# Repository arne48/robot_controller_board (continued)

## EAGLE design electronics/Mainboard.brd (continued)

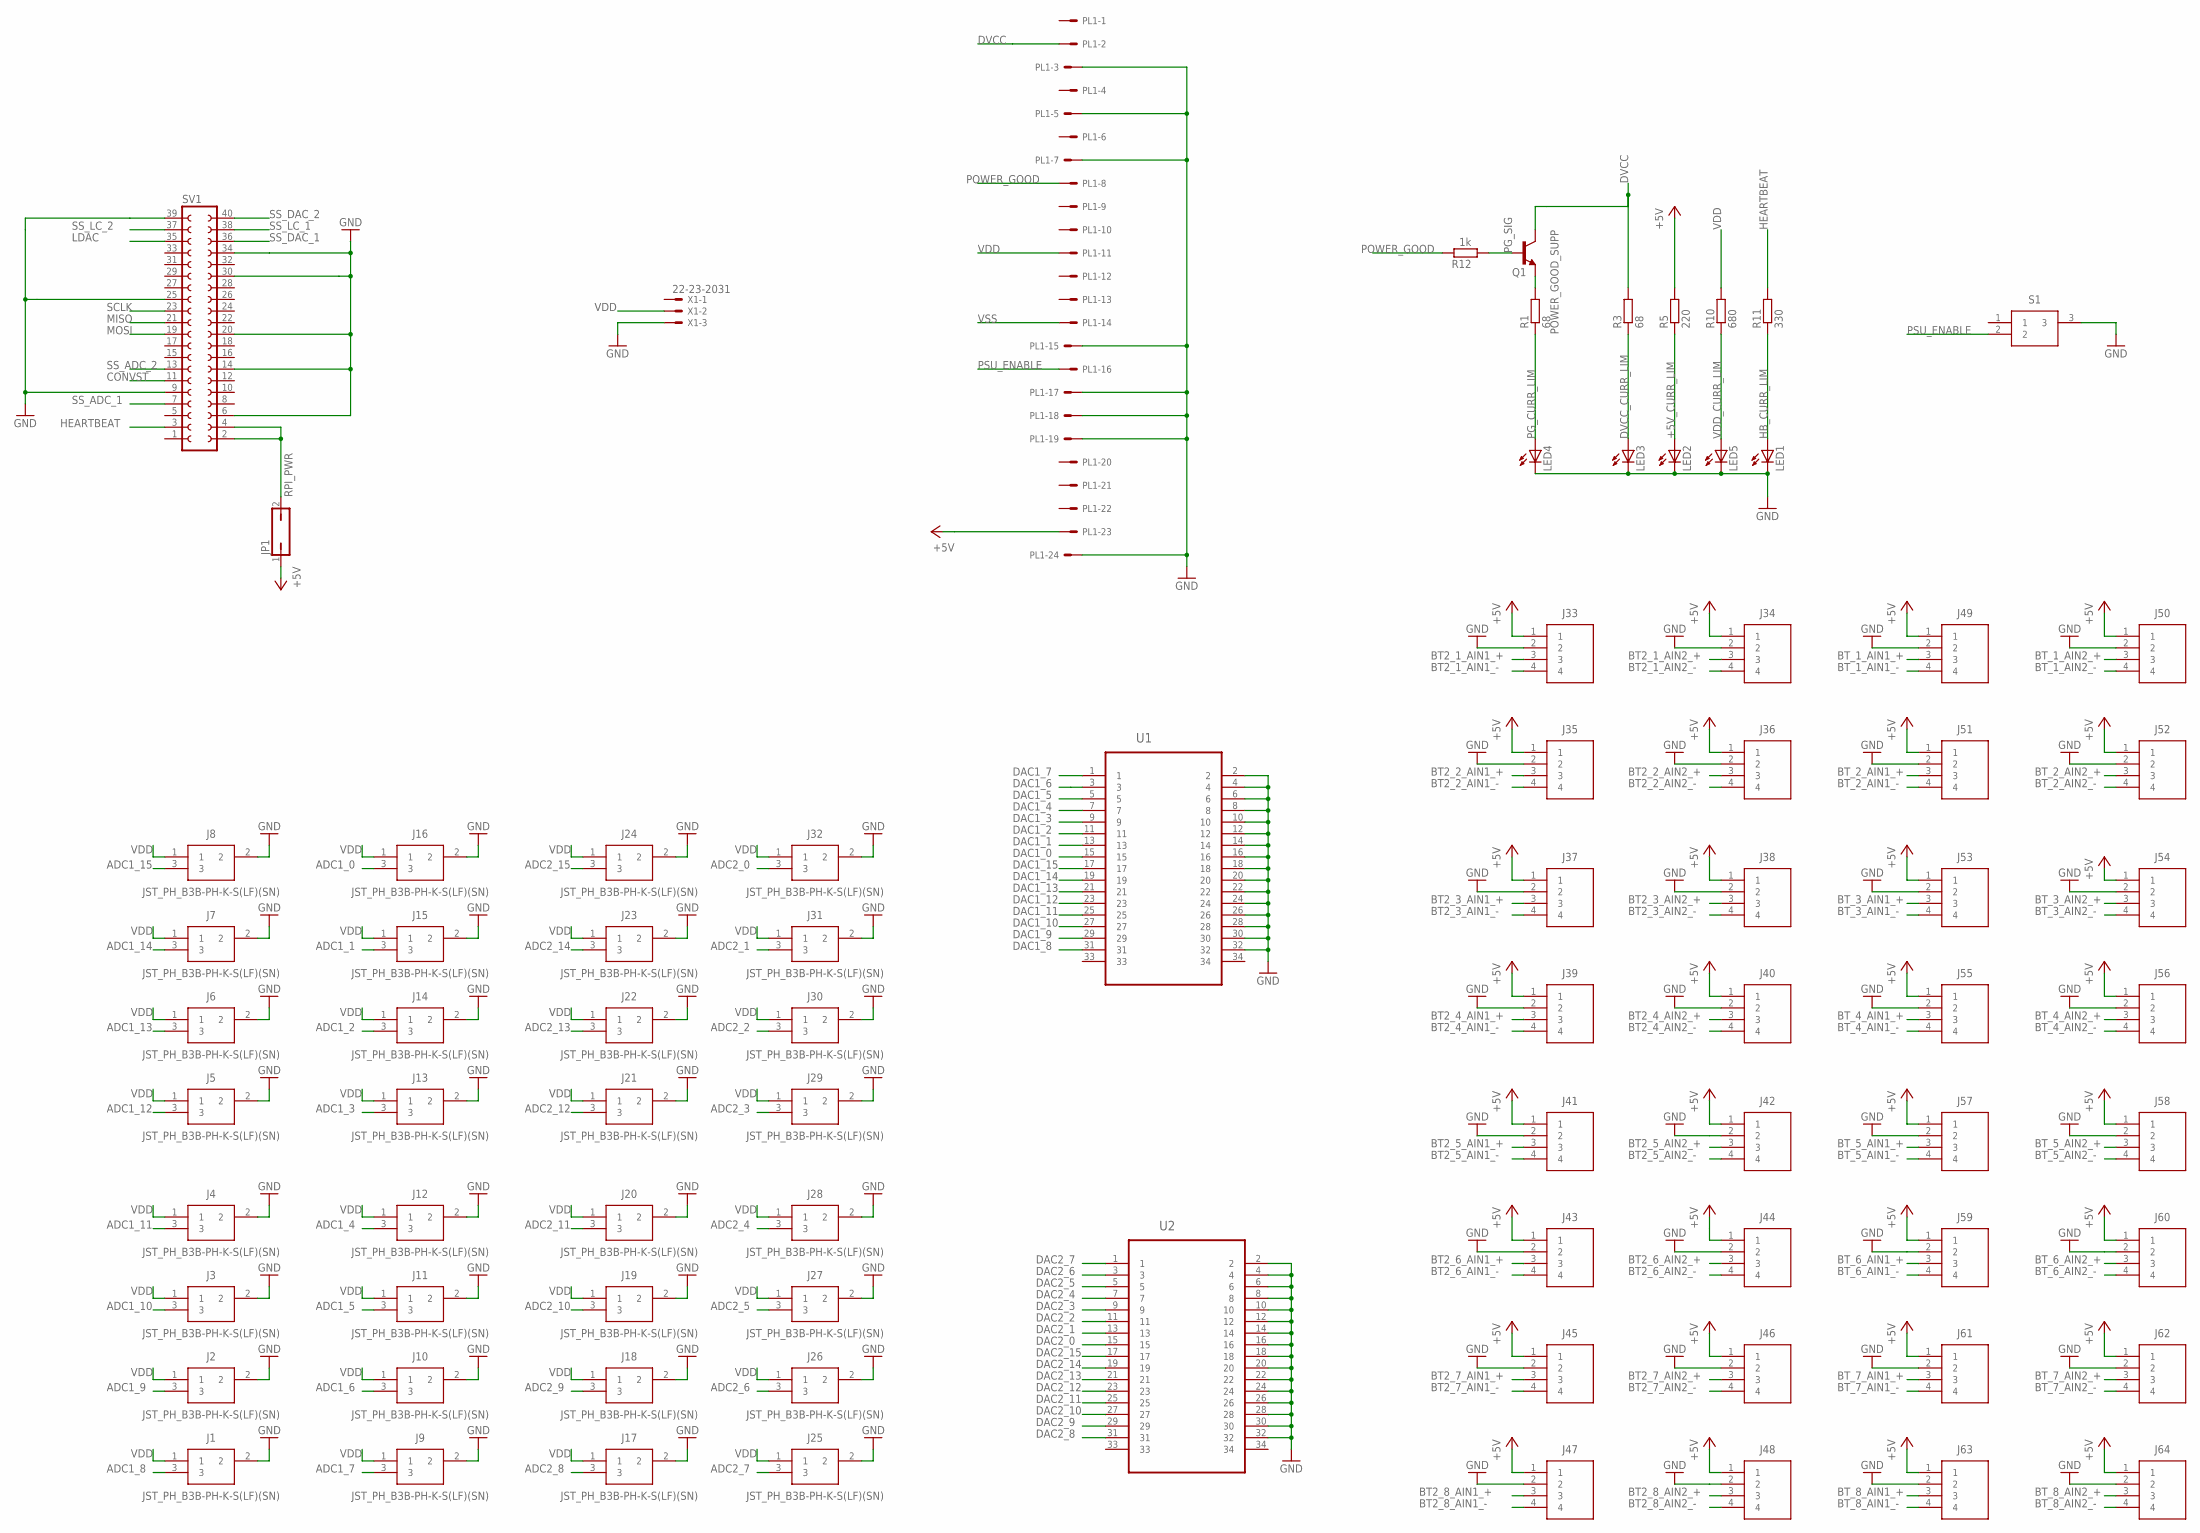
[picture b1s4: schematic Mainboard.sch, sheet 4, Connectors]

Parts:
J1, J2, J3, J4, J5, J6, J7, J8, J9, J10, J11, J12, J13, J14, J15, J16, J17, J18, J19, J20, J21, J22, J23, J24, J25, J26, J27, J28, J29, J30, J31, J32: JST_PH_B3B-PH-K-S(LF)(SN); JST_PH_SHDR3W50P0X200_1X3_790X450X600
J33, J34, J35, J36, J37, J38, J39, J40, J41, J42, J43, J44, J45, J46, J47, J48, J49, J50, J51, J52, J53, J54, J55, J56, J57, J58, J59, J60, J61, J62, J63, J64: B4B-PH-K-S(LF)(SN); SHDR4W50P0X200_1X4_990X450X600
JP1: JP1Q; JP1
LED1, LED2, LED3, LED4, LED5: LEDCHIP-LED0603; CHIP-LED0603
PL1: 555X-24V; 5566-24
Q1: BCF29SMD; SOT23-BEC
R1, R3: 68; R0805
R5: 220; R0805
R10: 680; R0805
R11: 330; R0805
R12: 1k; R0805
S1: 1MS1T1B1M2QES-5
SV1: FE20-2
U1, U2: AMP-5103309-7-34PIN_5103309-7; AMP-5103309-7-34PIN_TYCO_5103309-7
X1: 22-23-2031

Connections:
+5V: J33.1, J34.1, J35.1, J36.1, J37.1, J38.1, J39.1, J40.1, J41.1, J42.1, J43.1, J44.1, J45.1, J46.1, J47.1, J48.1, J49.1, J50.1, J51.1, J52.1, J53.1, J54.1, J55.1, J56.1, J57.1, J58.1, J59.1, J60.1, J61.1, J62.1, J63.1, J64.1, JP1.1, PL1.23, R5.2; also elsewhere on the board
+5V_CURR_LIM: LED2.A, R5.1
ADC1_0: J16.3; also elsewhere on the board
ADC1_1: J15.3; also elsewhere on the board
ADC1_2: J14.3; also elsewhere on the board
ADC1_3: J13.3; also elsewhere on the board
ADC1_4: J12.3; also elsewhere on the board
ADC1_5: J11.3; also elsewhere on the board
ADC1_6: J10.3; also elsewhere on the board
ADC1_7: J9.3; also elsewhere on the board
ADC1_8: J1.3; also elsewhere on the board
ADC1_9: J2.3; also elsewhere on the board
ADC1_10: J3.3; also elsewhere on the board
ADC1_11: J4.3; also elsewhere on the board
ADC1_12: J5.3; also elsewhere on the board
ADC1_13: J6.3; also elsewhere on the board
ADC1_14: J7.3; also elsewhere on the board
ADC1_15: J8.3; also elsewhere on the board
ADC2_0: J32.3; also elsewhere on the board
ADC2_1: J31.3; also elsewhere on the board
ADC2_2: J30.3; also elsewhere on the board
ADC2_3: J29.3; also elsewhere on the board
ADC2_4: J28.3; also elsewhere on the board
ADC2_5: J27.3; also elsewhere on the board
ADC2_6: J26.3; also elsewhere on the board
ADC2_7: J25.3; also elsewhere on the board
ADC2_8: J17.3; also elsewhere on the board
ADC2_9: J18.3; also elsewhere on the board
ADC2_10: J19.3; also elsewhere on the board
ADC2_11: J20.3; also elsewhere on the board
ADC2_12: J21.3; also elsewhere on the board
ADC2_13: J22.3; also elsewhere on the board
ADC2_14: J23.3; also elsewhere on the board
ADC2_15: J24.3; also elsewhere on the board
BT2_1_AIN1_+: J33.3; also elsewhere on the board
BT2_1_AIN1_-: J33.4; also elsewhere on the board
BT2_1_AIN2_+: J34.3; also elsewhere on the board
BT2_1_AIN2_-: J34.4; also elsewhere on the board
BT2_2_AIN1_+: J35.3; also elsewhere on the board
BT2_2_AIN1_-: J35.4; also elsewhere on the board
BT2_2_AIN2_+: J36.3; also elsewhere on the board
BT2_2_AIN2_-: J36.4; also elsewhere on the board
BT2_3_AIN1_+: J37.3; also elsewhere on the board
BT2_3_AIN1_-: J37.4; also elsewhere on the board
BT2_3_AIN2_+: J38.3; also elsewhere on the board
BT2_3_AIN2_-: J38.4; also elsewhere on the board
BT2_4_AIN1_+: J39.3; also elsewhere on the board
BT2_4_AIN1_-: J39.4; also elsewhere on the board
BT2_4_AIN2_+: J40.3; also elsewhere on the board
BT2_4_AIN2_-: J40.4; also elsewhere on the board
BT2_5_AIN1_+: J41.3; also elsewhere on the board
BT2_5_AIN1_-: J41.4; also elsewhere on the board
BT2_5_AIN2_+: J42.3; also elsewhere on the board
BT2_5_AIN2_-: J42.4; also elsewhere on the board
BT2_6_AIN1_+: J43.3; also elsewhere on the board
BT2_6_AIN1_-: J43.4; also elsewhere on the board
BT2_6_AIN2_+: J44.3; also elsewhere on the board
BT2_6_AIN2_-: J44.4; also elsewhere on the board
BT2_7_AIN1_+: J45.3; also elsewhere on the board
BT2_7_AIN1_-: J45.4; also elsewhere on the board
BT2_7_AIN2_+: J46.3; also elsewhere on the board
BT2_7_AIN2_-: J46.4; also elsewhere on the board
BT2_8_AIN1_+: J47.3; also elsewhere on the board
BT2_8_AIN1_-: J47.4; also elsewhere on the board
BT2_8_AIN2_+: J48.3; also elsewhere on the board
BT2_8_AIN2_-: J48.4; also elsewhere on the board
BT_1_AIN1_+: J49.3; also elsewhere on the board
BT_1_AIN1_-: J49.4; also elsewhere on the board
BT_1_AIN2_+: J50.3; also elsewhere on the board
BT_1_AIN2_-: J50.4; also elsewhere on the board
BT_2_AIN1_+: J51.3; also elsewhere on the board
BT_2_AIN1_-: J51.4; also elsewhere on the board
BT_2_AIN2_+: J52.3; also elsewhere on the board
BT_2_AIN2_-: J52.4; also elsewhere on the board
BT_3_AIN1_+: J53.3; also elsewhere on the board
BT_3_AIN1_-: J53.4; also elsewhere on the board
BT_3_AIN2_+: J54.3; also elsewhere on the board
BT_3_AIN2_-: J54.4; also elsewhere on the board
BT_4_AIN1_+: J55.3; also elsewhere on the board
BT_4_AIN1_-: J55.4; also elsewhere on the board
BT_4_AIN2_+: J56.3; also elsewhere on the board
BT_4_AIN2_-: J56.4; also elsewhere on the board
BT_5_AIN1_+: J57.3; also elsewhere on the board
BT_5_AIN1_-: J57.4; also elsewhere on the board
BT_5_AIN2_+: J58.3; also elsewhere on the board
BT_5_AIN2_-: J58.4; also elsewhere on the board
BT_6_AIN1_+: J59.3; also elsewhere on the board
BT_6_AIN1_-: J59.4; also elsewhere on the board
BT_6_AIN2_+: J60.3; also elsewhere on the board
BT_6_AIN2_-: J60.4; also elsewhere on the board
BT_7_AIN1_+: J61.3; also elsewhere on the board
BT_7_AIN1_-: J61.4; also elsewhere on the board
BT_7_AIN2_+: J62.3; also elsewhere on the board
BT_7_AIN2_-: J62.4; also elsewhere on the board
BT_8_AIN1_+: J63.3; also elsewhere on the board
BT_8_AIN1_-: J63.4; also elsewhere on the board
BT_8_AIN2_+: J64.3; also elsewhere on the board
BT_8_AIN2_-: J64.4; also elsewhere on the board
CONVST: SV1.11; also elsewhere on the board
DAC1_0: U1.15; also elsewhere on the board
DAC1_1: U1.13; also elsewhere on the board
DAC1_2: U1.11; also elsewhere on the board
DAC1_3: U1.9; also elsewhere on the board
DAC1_4: U1.7; also elsewhere on the board
DAC1_5: U1.5; also elsewhere on the board
DAC1_6: U1.3; also elsewhere on the board
DAC1_7: U1.1; also elsewhere on the board
DAC1_8: U1.31; also elsewhere on the board
DAC1_9: U1.29; also elsewhere on the board
DAC1_10: U1.27; also elsewhere on the board
DAC1_11: U1.25; also elsewhere on the board
DAC1_12: U1.23; also elsewhere on the board
DAC1_13: U1.21; also elsewhere on the board
DAC1_14: U1.19; also elsewhere on the board
DAC1_15: U1.17; also elsewhere on the board
DAC2_0: U2.15; also elsewhere on the board
DAC2_1: U2.13; also elsewhere on the board
DAC2_2: U2.11; also elsewhere on the board
DAC2_3: U2.9; also elsewhere on the board
DAC2_4: U2.7; also elsewhere on the board
DAC2_5: U2.5; also elsewhere on the board
DAC2_6: U2.3; also elsewhere on the board
DAC2_7: U2.1; also elsewhere on the board
DAC2_8: U2.31; also elsewhere on the board
DAC2_9: U2.29; also elsewhere on the board
DAC2_10: U2.27; also elsewhere on the board
DAC2_11: U2.25; also elsewhere on the board
DAC2_12: U2.23; also elsewhere on the board
DAC2_13: U2.21; also elsewhere on the board
DAC2_14: U2.19; also elsewhere on the board
DAC2_15: U2.17; also elsewhere on the board
DVCC: PL1.2, Q1.C, R3.2; also elsewhere on the board
DVCC_CURR_LIM: LED3.A, R3.1
GND: J1.2, J2.2, J3.2, J4.2, J5.2, J6.2, J7.2, J8.2, J9.2, J10.2, J11.2, J12.2, J13.2, J14.2, J15.2, J16.2, J17.2, J18.2, J19.2, J20.2, J21.2, J22.2, J23.2, J24.2, J25.2, J26.2, J27.2, J28.2, J29.2, J30.2, J31.2, J32.2, J33.2, J34.2, J35.2, J36.2, J37.2, J38.2, J39.2, J40.2, J41.2, J42.2, J43.2, J44.2, J45.2, J46.2, J47.2, J48.2, J49.2, J50.2, J51.2, J52.2, J53.2, J54.2, J55.2, J56.2, J57.2, J58.2, J59.2, J60.2, J61.2, J62.2, J63.2, J64.2, LED1.C, LED2.C, LED3.C, LED4.C, LED5.C, PL1.3, PL1.5, PL1.7, PL1.15, PL1.17, PL1.18, PL1.19, PL1.24, S1.3, SV1.6, SV1.9, SV1.14, SV1.20, SV1.25, SV1.30, SV1.34, SV1.39, U1.2, U1.4, U1.6, U1.8, U1.10, U1.12, U1.14, U1.16, U1.18, U1.20, U1.22, U1.24, U1.26, U1.28, U1.30, U1.32, U2.2, U2.4, U2.6, U2.8, U2.10, U2.12, U2.14, U2.16, U2.18, U2.20, U2.22, U2.24, U2.26, U2.28, U2.30, U2.32, X1.3; also elsewhere on the board
HB_CURR_LIM: LED1.A, R11.1
HEARTBEAT: R11.2, SV1.3
LDAC: SV1.35; also elsewhere on the board
MISO: SV1.21; also elsewhere on the board
MOSI: SV1.19; also elsewhere on the board
PG_CURR_LIM: LED4.A, R1.1
PG_SIG: Q1.B, R12.1
POWER_GOOD: PL1.8, R12.2
POWER_GOOD_SUPP: Q1.E, R1.2
PSU_ENABLE: PL1.16, S1.2
RPI_PWR: JP1.2, SV1.2, SV1.4
SCLK: SV1.23; also elsewhere on the board
SS_ADC_1: SV1.7; also elsewhere on the board
SS_ADC_2: SV1.13; also elsewhere on the board
SS_DAC_1: SV1.36; also elsewhere on the board
SS_DAC_2: SV1.40; also elsewhere on the board
SS_LC_1: SV1.38; also elsewhere on the board
SS_LC_2: SV1.37; also elsewhere on the board
VDD: J1.1, J2.1, J3.1, J4.1, J5.1, J6.1, J7.1, J8.1, J9.1, J10.1, J11.1, J12.1, J13.1, J14.1, J15.1, J16.1, J17.1, J18.1, J19.1, J20.1, J21.1, J22.1, J23.1, J24.1, J25.1, J26.1, J27.1, J28.1, J29.1, J30.1, J31.1, J32.1, PL1.11, R10.2, X1.2; also elsewhere on the board
VDD_CURR_LIM: LED5.A, R10.1
VSS: PL1.14; also elsewhere on the board

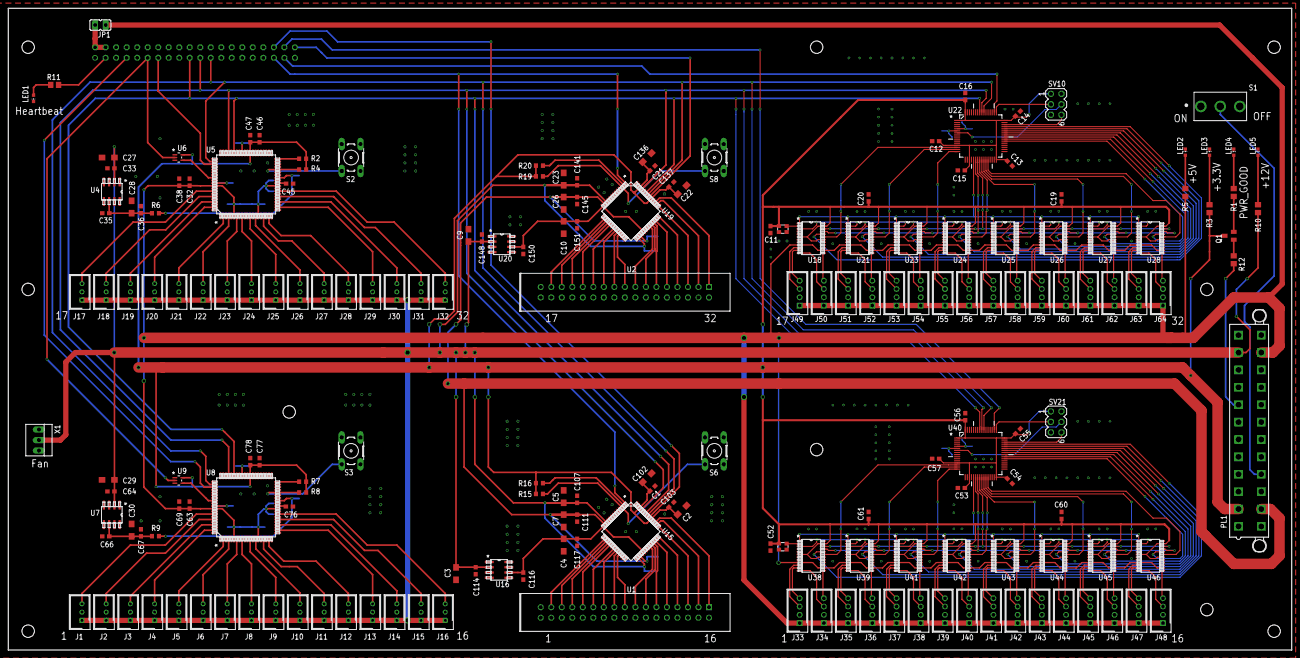
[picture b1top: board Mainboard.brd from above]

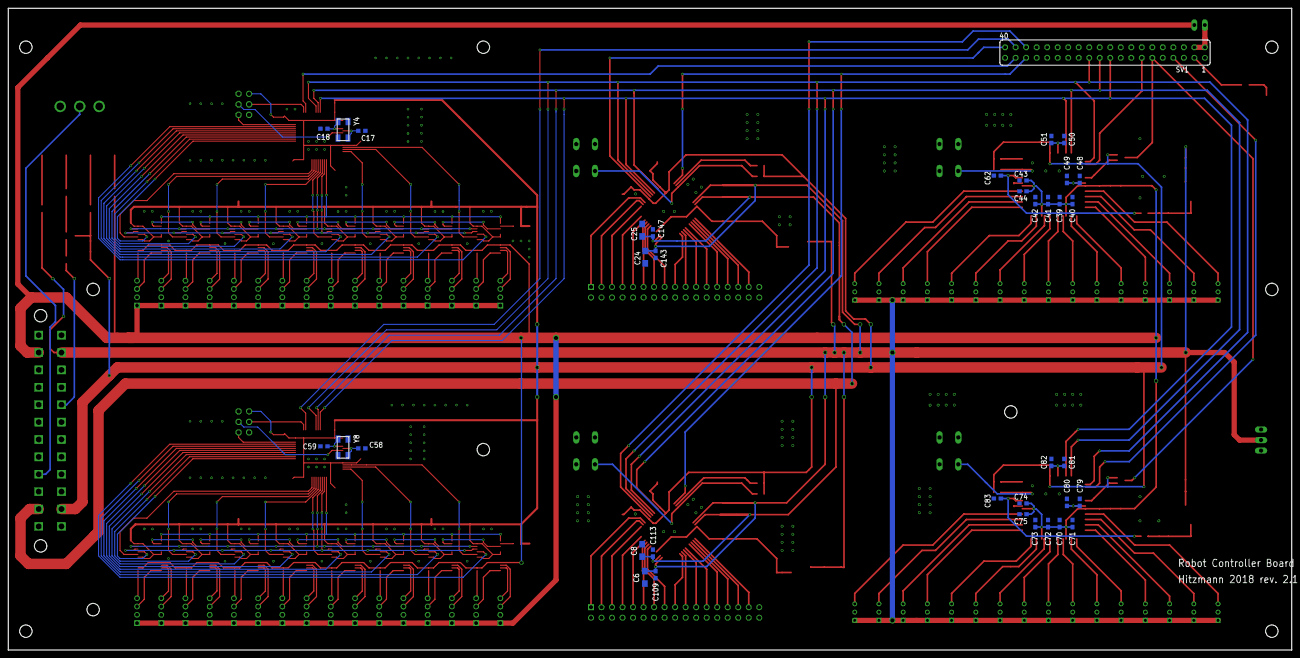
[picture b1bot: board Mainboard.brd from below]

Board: 2 copper layers, 310.0 x 155.0 mm, 227 parts (37 on the bottom side), 241 nets.

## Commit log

2018-04-17 added firmware repository as submodule
2018-04-17 first changes to the load cell section on the board
2018-04-18 reworked second load cell section
2018-04-18 load cell sections done
2018-04-18 reworked first dac
2018-04-18 functional state
2018-04-18 normalized text sizes
2018-04-19 finished layout
2018-04-19 added missing trace names
2018-04-19 minor changes on names and routing
2018-04-23 minor re-routing
2018-04-23 minor re-routing around the ADCs to spread ground plane further
2018-04-23 fixed ill-aligned trace
2018-04-28 minor silkscreen changes
2018-04-30 switched to smd leds
2018-05-18 re-routed spi bus
2018-05-21 reworked vias
2018-05-31 added more gnd connecting vias
2018-07-27 cleaned pcb and updated firmware version
